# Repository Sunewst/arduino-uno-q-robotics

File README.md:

## Arduino Uno Q Robotics Shield

> [!NOTE]
> Currently, I am unsure what pin on the Arduino Uno Q would connect to pin 17 on the camera connectors.
> 
> I choose SOC_GPIO_18, but there could be a correct pin that I wasn't able to find in the linux device tree of the Uno Q.
> 
> Once I am sure of which pin goes in pin 17 of the camera connector, I will add the second camera connector.
---
## DigiKey part list
https://www.digikey.com/en/mylists/list/X6XMV7FS3B

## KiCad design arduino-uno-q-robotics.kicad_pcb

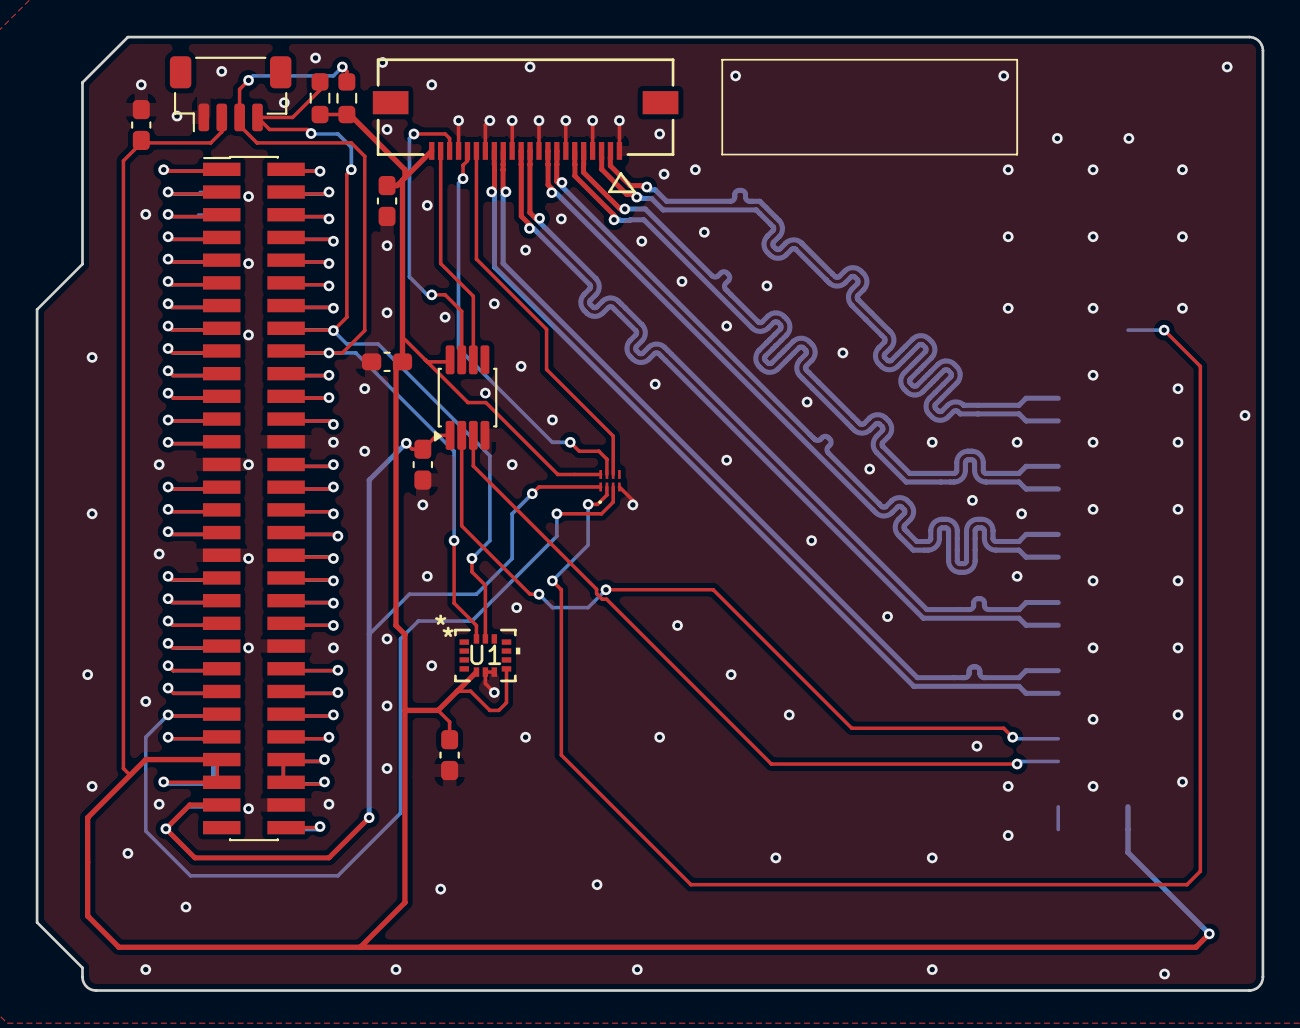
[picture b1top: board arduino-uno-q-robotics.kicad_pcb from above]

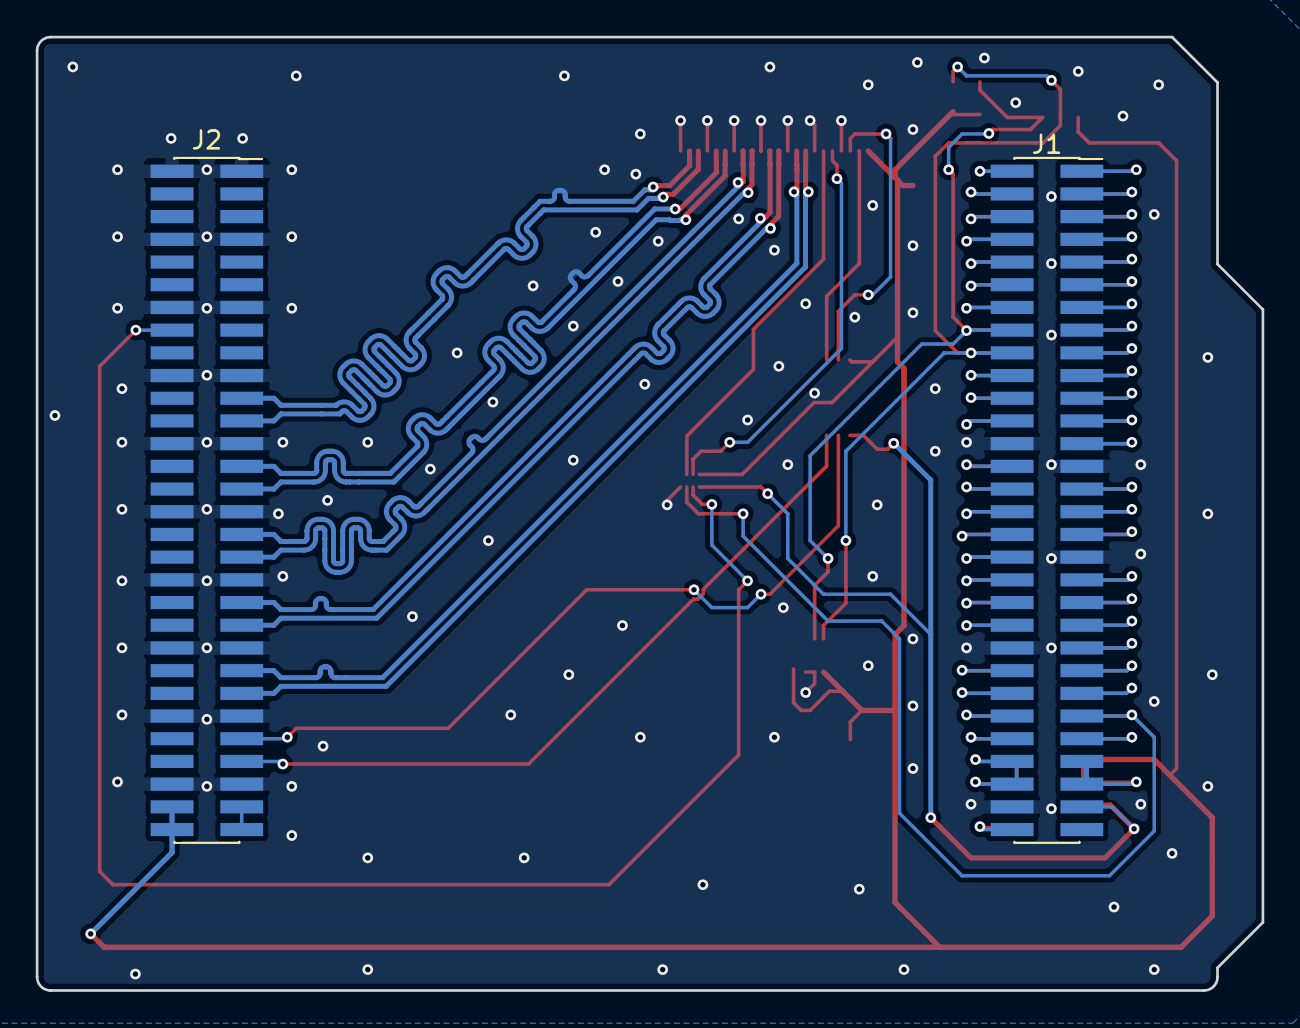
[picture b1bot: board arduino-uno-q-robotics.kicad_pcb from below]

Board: 4 copper layers, 68.6 x 53.3 mm, 15 parts (2 on the bottom side), 71 nets.

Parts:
C1, C3, C4, C5, C6: 0.1 uF; C_0603_1608Metric_Pad1.08x0.95mm_HandSolder
J1, J2: Conn_02x30_Odd_Even; PinHeader_2x30_P1.27mm_Vertical_SMD
J3: Connector_FFC-FPC; CON_5051102291_MOL
J5: Conn_02x30_Odd_Even; PinSocket_2x30_P1.27mm_Vertical_SMD
R1, R2: 10k; R_0603_1608Metric_Pad0.98x0.95mm_HandSolder
U1: LSM6DSO32; LGA-14L_2P5X3X0P83_STM
U2: TCA9803; VSSOP-8_3x3mm_P0.65mm
U3: JST_SH_BM04B-SRSS-TB_1x04-1MP_P1.00mm_Vertical
U6: 74LVC2T45GS115

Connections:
+1V8: C6.1, J1.57, J5.57, U2.1 (VCCA), U6.1 (VCCA)
+3.3V: C1.1, C3.1, C4.1, C5.1, J1.53, J1.55, J2.58, J2.60, J3.22, J5.53, J5.55, R1.1, R2.1, U1.5 (VDDIO), U1.8 (VDD), U2.8 (VCCB), U3.2 (3.3V), U6.8 (VCCB)
/CCI_I2C_SCL0: J2.51, U2.2 (SCLA)
/CCI_I2C_SDA0: J2.53, U2.3 (SDAA)
/CSI0_CLK_N: J2.33, J3.8
/CSI0_CLK_P: J2.35, J3.9
/CSI0_LN0_N: J2.21, J3.2
/CSI0_LN0_P: J2.23, J3.3
/CSI0_LN1_N: J2.27, J3.5
/CSI0_LN1_P: J2.29, J3.6
/CSI0_LN2_N: J2.39, J3.11
/CSI0_LN2_P: J2.41, J3.12
/CSI0_LN3_N: J2.45, J3.14
/CSI0_LN3_P: J2.47, J3.15
/EAR_M_R: J1.30, J5.30
/EAR_P_R: J1.28, J5.28
/HPH_L: J1.36, J5.36
/HPH_R: J1.38, J5.38
/HPH_REF: J1.40, J5.40
/HS_DET: J1.42, J5.42
/LINEOUT_M: J1.34, J5.34
/LINEOUT_P: J1.32, J5.32
/MCU_CRS_SYNC: J1.25, J5.25
/MCU_I2C4_SCL: J1.16, J5.16, R1.2, U1.13 (SCL), U3.4 (SCL)
/MCU_I2C4_SDA: J1.18, J5.18, R2.2, U1.14 (SDA), U3.3 (SDA)
/MCU_MCO: J1.23, J5.23
/MCU_OPAMP1_VINM: J1.24, J5.24
/MCU_OPAMP1_VINP: J1.22, J5.22
/MCU_OPAMP1_VOUT: J1.20, J5.20
/MCU_PE7: J1.12, J5.12
/MCU_PE8: J1.14, J5.14
/MCU_PSSI_D0: J1.1, J5.1
/MCU_PSSI_D1: J1.3, J5.3
/MCU_PSSI_D2: J1.5, J5.5
/MCU_PSSI_D3: J1.7, J5.7
/MCU_PSSI_D4: J1.9, J5.9
/MCU_PSSI_D5: J1.11, J5.11
/MCU_PSSI_D6: J1.13, J5.13
/MCU_PSSI_D7: J1.15, J5.15
/MCU_PSSI_DE: J1.21, J5.21
/MCU_PSSI_PDCK: J1.17, J5.17
/MCU_PSSI_RDY: J1.19, J5.19
/MCU_SDMMC1_CMD: J1.2, J5.2
/MCU_TRACE_CLK: J1.4, J5.4
/MCU_TRACE_D0: J1.6, J5.6
/MCU_TRACE_D2: J1.8, J5.8
/MCU_TRACE_D3: J1.10, J5.10
/MIC2_BIAS: J1.33, J5.33
/MIC2_INM: J1.31, J5.31
/MIC2_INP: J1.29, J5.29
/SCL0_3.3V: J3.20, U2.7 (SCLB)
/SDA0_3.3V: J3.21, U2.6 (SDAB)
/SOC_CAM_MCLK0: J2.16, U6.2 (1A)
/SOC_CAM_MCLK0_3.3V: J3.18, U6.7 (1B)
/SOC_GPIO_0_SE0: J1.37, J5.37
/SOC_GPIO_1_SE0: J1.39, J5.39
/SOC_GPIO_2_SE0: J1.41, J5.41
/SOC_GPIO_3_SE0: J1.43, J5.43
/SOC_GPIO_18: J1.49, J5.49, U6.3 (2A)
/SOC_GPIO_18_3.3V: J3.17, U6.6 (2B)
/SOC_GPIO_28: J1.51, J5.51
/SOC_GPIO_82_SE0: J1.47, J5.47
/SOC_GPIO_86_SE0: J1.45, J5.45
/SOC_GPIO_98: J1.46, J5.46
/SOC_GPIO_99: J1.48, J5.48
/SOC_GPIO_100: J1.50, J5.50
/SOC_GPIO_101: J1.52, J5.52
GND: C1.2, C3.2, C4.2, C5.2, C6.2, J1.26, J1.27, J1.35, J1.44, J1.58, J2.1, J2.2, J2.7, J2.8, J2.13, J2.14, J2.19, J2.20, J2.25, J2.26, J2.31, J2.32, J2.37, J2.38, J2.43, J2.44, J2.49, J2.50, J2.55, J2.56, J3.1, J3.4, J3.7, J3.10, J3.13, J3.16, J3.19, J5.26, J5.27, J5.35, J5.44, J5.58, U1.6 (GND), U1.7 (GND), U2.4 (GND), U3.1 (GND), U6.4 (GND)
VBAT: J1.60, J5.60
VBUS: J1.54, J1.56, J5.54, J5.56
VIN: J2.57, J2.59

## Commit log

2026-01-06 Adjust file structure
2026-01-06 Add 3D model to camera connectors
2026-01-06 Add Gyro/Accelerometer sensor
2026-01-07 Add I2C logic level shifter to schematic
2026-01-07 Adjust JMEDIA labels for differential routing
2026-01-07 Connect camera data lines to camera connector
2026-01-07 Add GND layers
2026-01-07 Add resistor footprint
    Resistor_SMD:R_0603_1608Metric_Pad0.98x0.95mm
2026-01-07 Change FPC footprint and 3D model
2026-01-08 Add PCB constraints
    Based on OSHPark 2-layer board
    Update constraints
2026-01-08 Update PCB constrains for 4 layer board
2026-01-08 Make board 4 layers
2026-01-08 Remove unused symbols/footprints
2026-01-08 Connect J3 camera header signals
2026-01-12 Switch JMEDIA header to THT version
2026-01-12 Adjust Differential Pair values
2026-01-13 Create STEMMA/JST port symbol
2026-01-13 Add STEMMA port to MCU I2C
2026-01-13 Adjust STEMMA port pin numbers
2026-01-13 Separate camera connectors level shifter
2026-01-13 Add a 3.3v power layer
2026-01-13 Add Pin sockets and headers for JMISC pins
2026-01-13 Add trace connections to JMISC 2.54 header
2026-01-13 Add STEMMA QT 3D model
2026-01-13 Connect magnet and stemma port
2026-01-14 Add GPIO voltage stepper IC files
2026-01-15 Add GPIO voltage steppers to schematic
2026-01-15 Add decoupling capacitors to schematic
2026-01-15 Adjust JMISC/JMEDIA header spacing
2026-01-15 Add missing components to PCB editor
2026-01-15 Fix DRC clearance issues
2026-01-16 Add male header for JMISC ports
2026-01-16 Adjust JMISC male headers position
2026-01-16 Add missing pin functions to JMISC/MEDIA
2026-01-16 Adjust power symbols
2026-01-16 Move silkscreen to fab layer
2026-01-16 Add BOM links to parts
2026-01-17 Fix DRC warnings/errors
    Fix DRC errors
2026-01-18 Organize schematic sheet
2026-01-20 Adjust MCLK traces/vias
2026-01-21 Adjust ground pour for front and back layer
2026-01-22 Edit README
2026-01-23 Remove male/female headers
2026-01-26 Add l298p IC and screw terminal
2026-01-31 Move placement of camera components
2026-02-01 Move camera 1 traces to back layer
2026-02-02 Reconnect MCLK0 to camera connector
2026-02-02 Adjust placement of decoups and pullup resistors
    Update arduino-uno-q-robotics.kicad_sch
2026-02-02 Move project files to main folder
2026-02-02 Adjust JMISC header position
2026-02-02 Add STEP file
2026-02-02 Adjust differential camera pairs length
2026-02-07 Add DigiKey part list
2026-03-01 Assign CSI1 lines to high speed netclass
2026-03-08 Adjust traces
2026-04-20 Update to KiCAD 10
